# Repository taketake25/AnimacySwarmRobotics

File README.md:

# StudySwarmRobotics
群ロボットの勉強のために、5cm角のを作成します。赤外線での近距離通信可能。

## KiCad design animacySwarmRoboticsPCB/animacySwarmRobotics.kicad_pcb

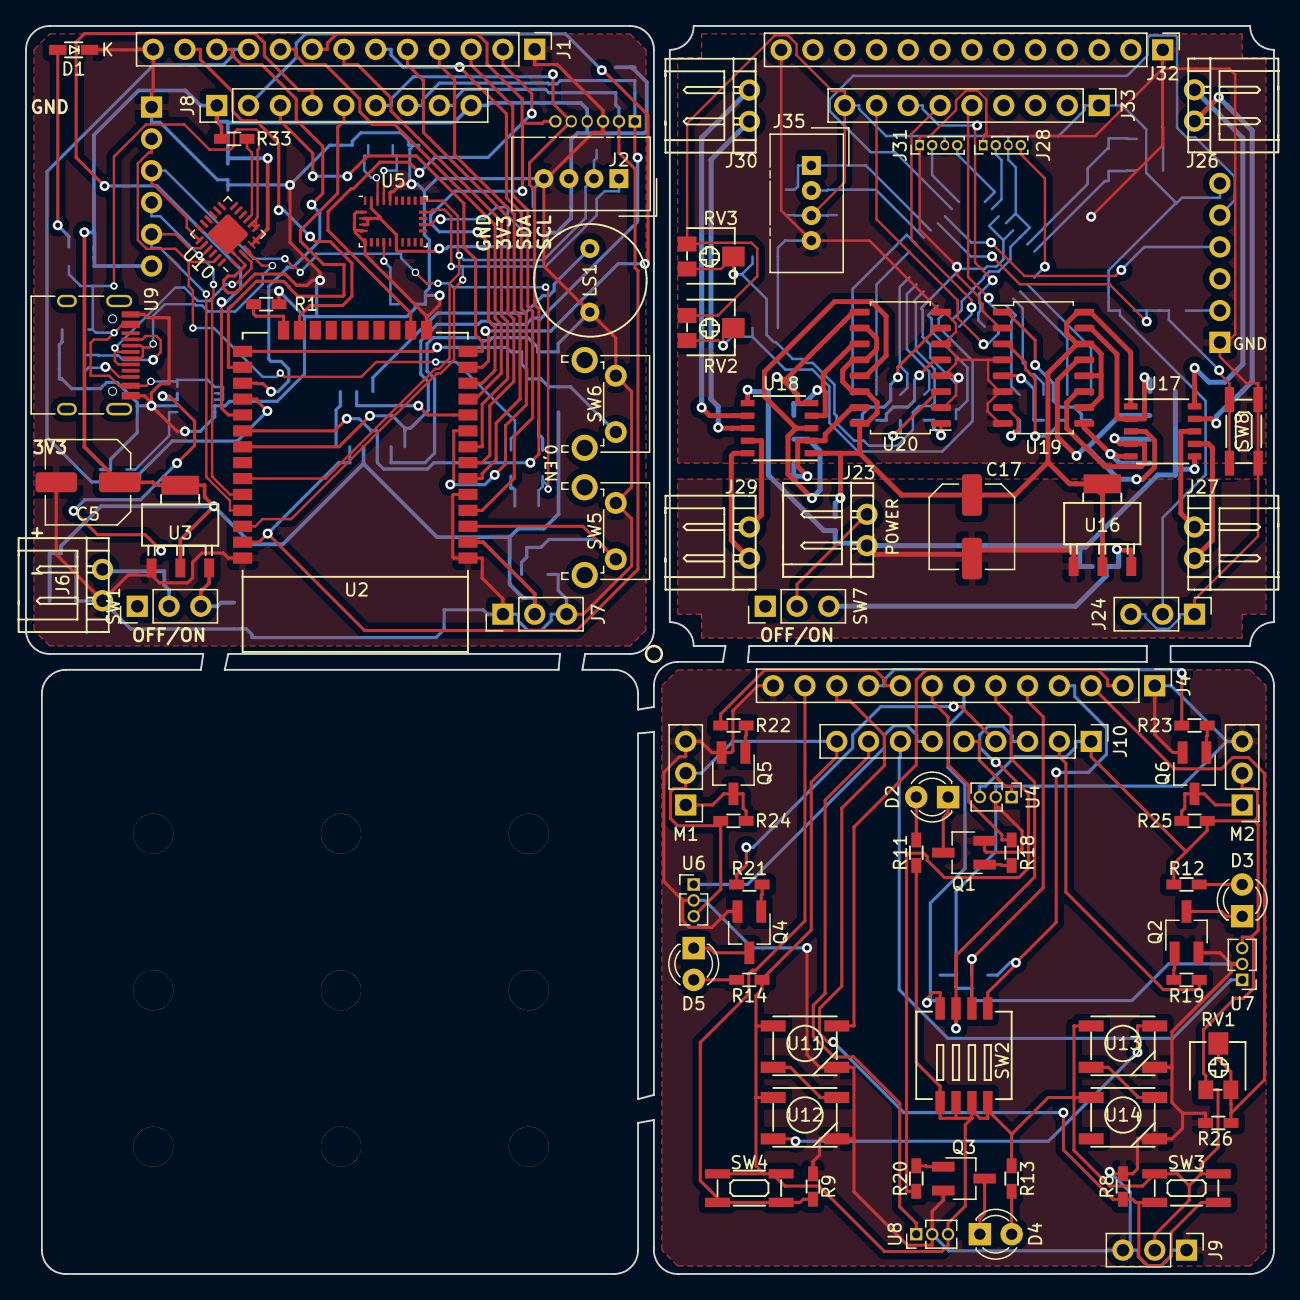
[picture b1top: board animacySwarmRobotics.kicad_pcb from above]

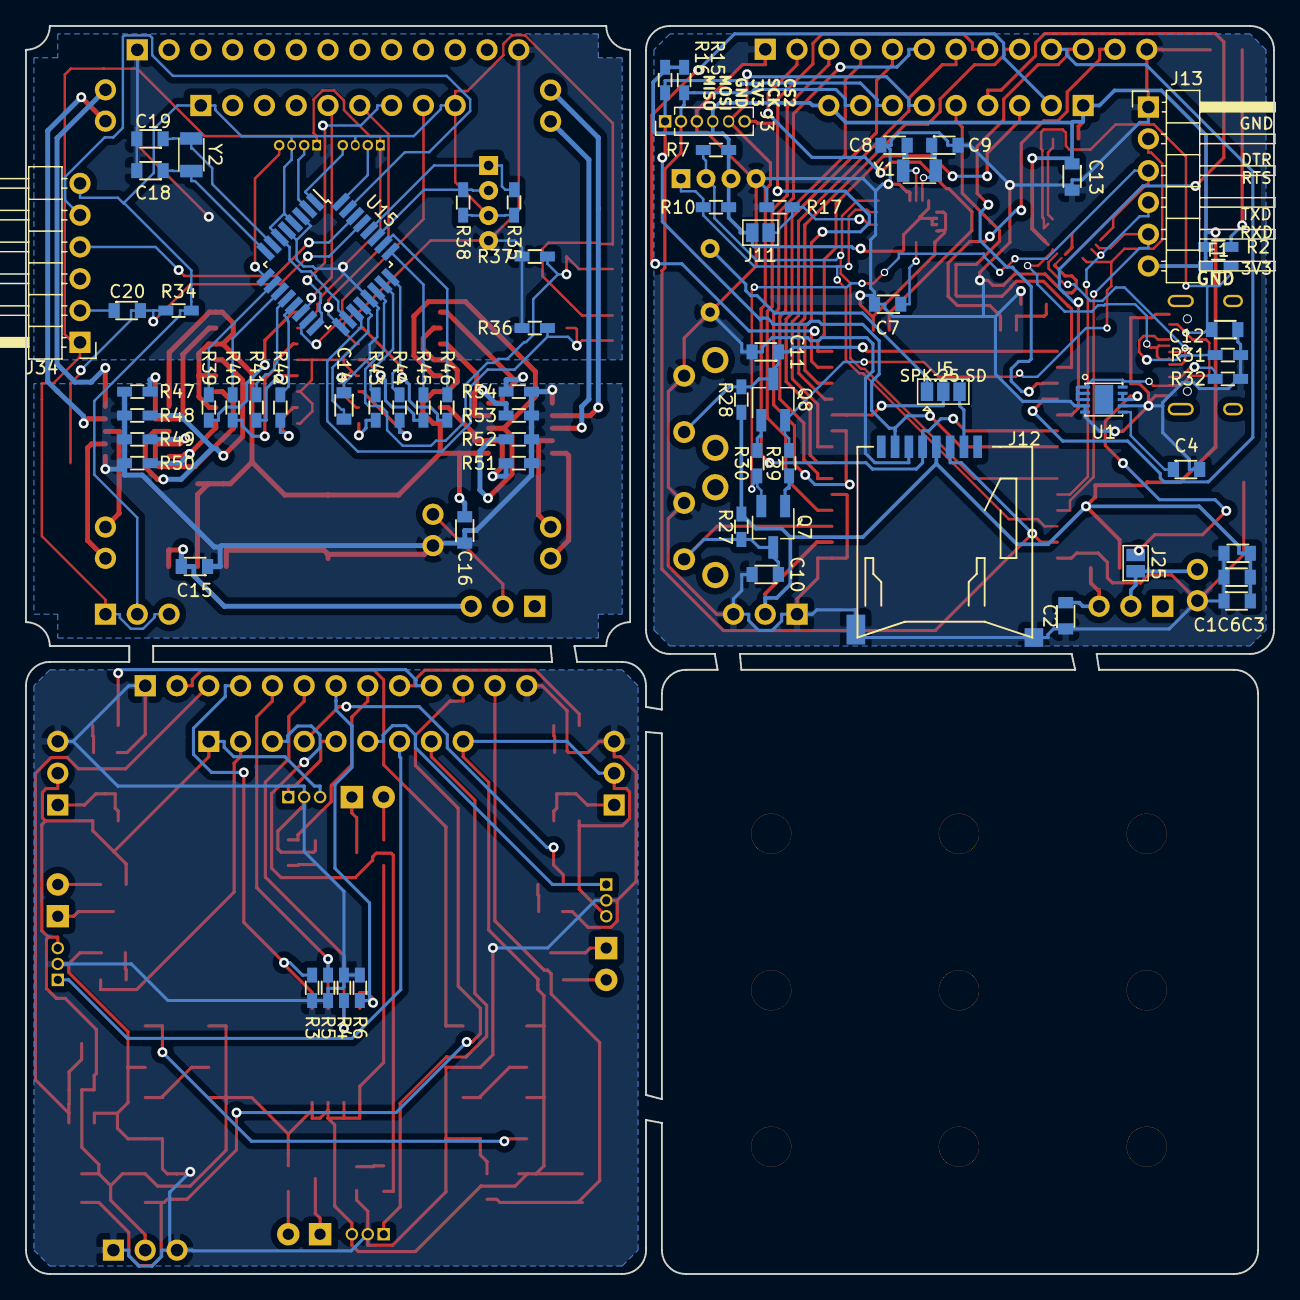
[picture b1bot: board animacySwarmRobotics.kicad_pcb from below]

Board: 2 copper layers, 99.7 x 99.7 mm, 159 parts (69 on the bottom side), 145 nets.

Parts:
C1: 1u; SMD-2012
C2, C3, C6, C15, C16: C; SMD-2012
C4, C7, C8, C9, C12, C13, C14, C18, C19, C20: C_Small; SMD-2012
C5, C17: CP; C_Elec_6.3x7.7
C10, C11: 1n; SMD-2012
D1: LED; 2012LED
D2, D3, D4, D5: LED; LED_D3.0mm
F1: Polyfuse_Small; SMD-1608
J1, J4, J32: Conn_01x13; PinHeader_1x13_P2.54mm_Vertical
J2, J35: Conn_01x04; NS-Tech_Grove_1x04_P2mm_Vertical
J3: Conn_01x06; PinHeader_1x06_P1.27mm_Vertical
J5: Conn_01x03; SolderJumper-3_P1.3mm_Open_Pad1.0x1.5mm
J6, J23, J26, J27, J29, J30: Conn_01x02; Connector_EH_2pin
J7, J9, J24: Conn_01x03; PinHeader_1x03_P2.54mm_Vertical
J8, J10, J33: Conn_01x09; PinHeader_1x09_P2.54mm_Vertical
J11, J25: Conn_01x02; SolderJumper-2_P1.3mm_Open_Pad1.0x1.5mm
J12: Micro_SD_Card_Det_Hirose_DM3AT; SD_DM3AT-SF-PEJMS
J13, J34: Conn_01x06; PinHeader_1x06_P2.54mm_Horizontal
J14, J15, J16, J17, J18, J19, J20, J21, J22: Conn_01x01; HOLE_3.2mm_nopad
J28, J31: Conn_01x04; PinHeader_1x04_P1.00mm_Vertical
LS1: Speaker; small_speaker
M1, M2: Motor_Servo; PinHeader_1x03_P2.54mm_Vertical
Q1, Q2, Q3, Q4, Q5, Q6, Q7, Q8: Q_NPN_BEC; SC-59_Handsoldering
R1, R28: 5K; SMD-1608
R2: 2K; SMD-1608
R3, R4, R5, R6: 1k; SMD-1608
R7, R10, R17: 2.2K; SMD-1608
R8, R9: 470; SMD-1608
R11, R12, R13, R14, R15, R16, R18, R19, R20, R21, R22, R23, R24, R25: R; SMD-1608
R26, R31, R32, R33, R34, R35, R36, R37, R38, R39, R40, R41, R42, R43, R44, R45, R46, R47, R48, R49, R50, R51, R52, R53, R54: 1K; SMD-1608
R27, R29, R30: 12K; SMD-1608
RV1, RV2, RV3: R_POT; S_POT_SMD
SW1, SW7: SW_SPDT; PinHeader_1x03_P2.54mm_Vertical
SW2: DIP_SW_4; EHS104LD
SW3, SW4, SW8: SW_Push; SMD_SW
SW5, SW6: SW_Push; SW_Tactile_SPST_Angled_PTS645Vx39-2LFS
U1: MCP73855T-I; MCP73855
U2: ESP32; ESP-WROOM-32
U3, U16: AMS1117CD-3.3; AZ1086H
U4, U6, U7, U8: OSRB38C9AA; PinHeader_1x03_P1.27mm_Vertical
U5: BNO085; LGA-28_5.2x3.8mm_P0.5mm
U9: TypeC; USB_C_Receptacle_HRO_TYPE-C-31-M-12
U10: CP2104; QFN-24-1EP_4x4mm_P0.5mm_EP2.6x2.6mm
U11, U12, U13, U14: WS2812B
U15: ATmega328P-AU; TQFP-32_7x7mm_P0.8mm
U17, U18: LV8548MC; SSOP-10_3.9x4.9mm_P1.00mm
U19, U20: TLP293-4; SOIC-16_4.55x10.3mm_P1.27mm
Y1, Y2: Crystal; FC-135

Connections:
+3V3: C1.2, C3.1, C5.1, C6.1, C13.2, F1.2, J2.3, J3.4, J7.2, J8.1, J8.9, J11.2, J12.4, J13.6, R2.2, R7.1, R10.1, R15.1, R16.1, R27.1, R28.2, R33.2, U2.2, U3.2, U5.3, U5.4, U5.11, U5.28, U10.5, U10.6
+6V: C2.1, SW1.3, U3.3
/CS1: J5.3, J12.2
/D+: U9.A6, U9.B6, U10.3
/D-: U9.A7, U9.B7, U10.4
/DTR: J13.2, Q8.2, R29.2, U10.23
/EN: C10.2, Q7.3, R27.2, SW5.2, U2.3
/IO0: C11.2, Q8.3, R28.1, SW6.2, U2.25
/IO2: R1.2, U2.24
/IO4: J8.5, U2.26
/IO5: J8.4, U2.29
/IO12: J8.3, U2.14
/IO14: J8.2, U2.13
/IO15: J1.12, U2.23
/IO16: J1.11, U2.27
/IO17: J1.10, U2.28
/IO25: J5.2, U2.10
/IO26: J1.9, U2.11
/IO27: J1.8, J3.6, U2.12
/IO32: J1.7, U2.8
/IO33: J1.6, U2.9
/IO34: J1.4, U2.6
/IO35: J1.5, U2.7
/LEDs: J1.2, U2.16
/LiPo+: J6.2, J25.2, SW1.2
/MISO: J3.1, J8.7, J12.7, R16.2, U2.31
/MOSI: J3.2, J8.8, J12.3, R15.2, U2.37
/POT1: J1.3, U2.4
/RTS: J13.3, Q7.2, R30.2, U10.19
/RXD: J13.5, U2.35, U10.20
/S3V3: J9.2, J10.1, J10.9, M1.2, M2.2, R11.1, R12.1, R13.1, R14.1, R24.1, R25.1, RV1.1, SW2.1, SW2.2, SW2.3, SW2.4, SW3.1, SW4.1, U4.3, U6.3, U7.3, U8.3, U11.1, U12.1, U13.1, U14.1
/SCK: J3.5, J8.6, J12.5, U2.30
/SCL: J2.1, R10.2, U2.36, U5.19
/SDA: J2.2, R7.2, U2.33, U5.20
/SDIP1: J4.4, R3.1, SW2.8
/SDIP2: J4.5, R5.1, SW2.7
/SDIP3: J4.6, R4.1, SW2.6
/SDIP4: J4.7, R6.1, SW2.5
/SGND: J4.1, J4.13, J9.1, J9.3, M1.3, M2.3, Q1.2, Q2.2, Q3.2, Q4.2, Q5.2, Q6.2, R3.2, R4.2, R5.2, R6.2, R8.2, R9.2, R26.2, U4.2, U6.2, U7.2, U8.2, U11.3, U12.3, U13.3, U14.3
/SIR1: J4.8, R18.1
/SIR2: J10.2, R19.1
/SIR3: J10.3, R20.1
/SIR4: J10.4, R21.1
/SIRRecv1: J10.5, U4.1
/SIRRecv2: J10.6, U6.1
/SIRRecv3: J10.7, U7.1
/SIRRecv4: J10.8, U8.1
/SLEDs: J4.2, U11.4
/SPOT: J4.3, R26.1, RV1.2, RV1.3
/SSERVO1: J4.9, R22.1
/SSERVO2: J4.10, R23.1
/SSW1: J4.11, R8.1, SW3.2
/SSW2: J4.12, R9.1, SW4.2
/Speaker1: J5.1, LS1.2
/TXD: J13.4, U2.34, U10.21
/VBUS: C12.1, F1.1, U1.1, U1.2, U1.3, U1.10, U9.A4, U9.A9, U9.B4, U9.B9, U10.7, U10.8
/motorBase/3V34: J24.2, J28.3, J31.3, J33.1, J33.9, J34.6, J35.3, R34.1, R35.1, R38.1, RV2.1, RV3.1, U15.4, U15.6, U15.18
/motorBase/BLIN1: R43.1, U15.23
/motorBase/BLIN2: R44.1, U15.24
/motorBase/BRIN1: R45.1, U15.25
/motorBase/BRIN2: R46.1, U15.26
/motorBase/CS4: J33.5, U15.14
/motorBase/DTR4: C20.2, J34.2
/motorBase/ENC1A: J31.2, U15.32
/motorBase/ENC1B: J31.4, U15.1
/motorBase/ENC2A: J28.2, U15.2
/motorBase/ENC2B: J28.4, U15.9
/motorBase/FLIN1: R39.1, U15.10
/motorBase/FLIN2: R40.1, U15.11
/motorBase/FRIN1: R41.1, U15.12
/motorBase/FRIN2: R42.1, U15.13
/motorBase/GND4: C14.2, C18.1, C19.1, J24.1, J24.3, J28.1, J31.1, J32.1, J32.13, J34.1, J35.4, R36.2, R37.2, SW8.2, U15.3, U15.5, U15.21, U19.2, U19.4, U19.6, U19.8, U20.2, U20.4, U20.6, U20.8
/motorBase/M3V3: C16.1, C17.1, U16.2, U17.1, U18.1, U19.10, U19.12, U19.14, U19.16, U20.10, U20.12, U20.14, U20.16
/motorBase/MBLIN1: R51.1, U18.2, U20.15
/motorBase/MBLIN2: R52.1, U18.3, U20.13
/motorBase/MBLOUT1: J29.1, U18.10
/motorBase/MBLOUT2: J29.2, U18.9
/motorBase/MBRIN1: R53.1, U18.4, U20.11
/motorBase/MBRIN2: R54.1, U18.5, U20.9
/motorBase/MBROUT1: J30.1, U18.8
/motorBase/MBROUT2: J30.2, U18.7
/motorBase/MFLIN1: R47.1, U17.2, U19.15
/motorBase/MFLIN2: R48.1, U17.3, U19.13
/motorBase/MFLOUT1: J26.1, U17.10
/motorBase/MFLOUT2: J26.2, U17.9
/motorBase/MFRIN1: R49.1, U17.4, U19.11
/motorBase/MFRIN2: R50.1, U17.5, U19.9
/motorBase/MFROUT1: J27.1, U17.8
/motorBase/MFROUT2: J27.2, U17.7
/motorBase/MGND: C15.2, C16.2, C17.2, J23.1, R47.2, R48.2, R49.2, R50.2, R51.2, R52.2, R53.2, R54.2, U16.1, U17.6, U18.6
/motorBase/MISO4: J33.7, U15.16
/motorBase/MOSI4: J33.8, U15.15
/motorBase/MVcc: C15.1, SW7.3, U16.3
/motorBase/POT14: R36.1, RV2.2, RV2.3, U15.19
/motorBase/POT24: R37.1, RV3.2, RV3.3, U15.22
/motorBase/RXD4: J34.5, U15.31
/motorBase/SCK4: J33.6, U15.17
/motorBase/SCL4: J35.1, R35.2, U15.28
/motorBase/SDA4: J35.2, R38.2, U15.27
/motorBase/TXD4: J34.4, U15.30
GND: C1.1, C2.2, C3.2, C4.1, C5.2, C6.2, C7.1, C8.1, C9.1, C10.1, C11.1, C12.2, C13.1, D1.1, J1.1, J1.13, J2.4, J3.3, J6.1, J7.1, J7.3, J12.6, J12.11, J13.1, LS1.1, R1.1, R17.2, R31.2, R32.1, SW5.1, SW6.1, U1.4, U1.5, U1.7, U2.1, U2.5, U2.15, U2.38, U3.1, U5.2, U5.5, U5.6, U5.25, U9.A1, U9.A12, U9.B1, U9.B12, U10.2, U10.25
unnamed: C4.2, U1.6
unnamed: C7.2, U5.9
unnamed: C8.2, U5.26, Y1.1
unnamed: C9.2, U5.27, Y1.2
unnamed: C14.1, U15.20
unnamed: C18.2, U15.8, Y2.1
unnamed: C19.2, U15.7, Y2.2
unnamed: C20.1, R34.2, SW8.1, U15.29
unnamed: D1.2, R2.1
unnamed: D2.1, Q1.3
unnamed: D2.2, R11.2
unnamed: D3.1, Q2.3
unnamed: D3.2, R12.2
unnamed: D4.1, Q3.3
unnamed: D4.2, R13.2
unnamed: D5.1, Q4.3
unnamed: D5.2, R14.2
unnamed: J11.1, R17.1, U5.17
unnamed: J23.2, SW7.2
unnamed: J25.1, U1.8, U1.9
unnamed: M1.1, Q5.3, R24.2
unnamed: M2.1, Q6.3, R25.2
unnamed: Q1.1, R18.2
unnamed: Q2.1, R19.2
unnamed: Q3.1, R20.2
unnamed: Q4.1, R21.2
unnamed: Q5.1, R22.2
unnamed: Q6.1, R23.2
unnamed: Q7.1, R29.1
unnamed: Q8.1, R30.1
unnamed: R31.1, U9.A5
unnamed: R32.2, U9.B5
unnamed: R33.1, U10.9
unnamed: R39.2, U19.1
unnamed: R40.2, U19.3
unnamed: R41.2, U19.5
unnamed: R42.2, U19.7
unnamed: R43.2, U20.1
unnamed: R44.2, U20.3
unnamed: R45.2, U20.5
unnamed: R46.2, U20.7
unnamed: U11.2, U12.4
unnamed: U12.2, U13.4
unnamed: U13.2, U14.4

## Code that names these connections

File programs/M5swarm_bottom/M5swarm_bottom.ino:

#include <SPI.h>

// 3,5,6,9,10,11
#define FRIN1 8
//#define FRIN1 10 // PWM
#define FRIN2 9 // PWM
#define FLIN1 6 // PWM
#define FLIN2 7
//#define BLIN1 3 // PWM
#define BLIN1 14
#define BLIN2 15
//#define BRIN1 5 // PWM
#define BRIN1 16
#define BRIN2 17
#define SDA 18
#define SCL 19
//#define ENC1A 2 // ×
//#define ENC1B 3 // ×
#define ENC2A 4
//#define ENC2B 5 // ×
#define CS 10 // ×
//#define CS 2
#define MOSI 11
#define MISO 12
#define SCK 13
#define POT1 ADC6
#define POT2 ADC7


int count = 0;
unsigned long startTime = 0;
unsigned long timer = 0;
bool timerFlag = false;
int cmdSpeedReceived = 0;
int cmdDirecReceived = 0;
int cmdRotateReceived = 0;
bool moving = false;
bool rotating = false;
int8_t speed = 0;
int8_t speedMotors[8] = {0};
int8_t motorPins[8] = {FLIN2,FLIN1,FRIN1,FRIN2,BRIN2,BRIN1,BLIN1,BLIN2};


#define FRONT 0
#define BACK 1

uint8_t recvD;
uint8_t recvS;
uint8_t recvR;

void setup() {
  Serial.begin(115200);
  Serial.println("run!!");

  pinMode(CS, OUTPUT);
  SPCR |= bit(SPE);
  pinMode(MISO, OUTPUT);

  pinMode(FRIN1, OUTPUT);
  pinMode(FRIN2, OUTPUT);
  pinMode(FLIN1, OUTPUT);
  pinMode(FLIN2, OUTPUT);
  pinMode(BRIN1, OUTPUT);
  pinMode(BRIN2, OUTPUT);
  pinMode(BLIN1, OUTPUT);
  pinMode(BLIN2, OUTPUT);

  //  SPI.begin();
  //  SPI.beginTransaction(SPISetting(8000000, MSBFIRST, SPI_MODE3));
  SPI.attachInterrupt();
  startTime = millis();
}

ISR(SPI_STC_vect) {
//  cmdDirecReceived = false;
//  cmdSpeedReceived = false;
  switch (char(SPDR)) {
    case 's': cmdSpeedReceived = 1; break; // s
    case 'd': cmdDirecReceived = 1; break; // d
    case 'r': cmdRotateReceived = 1; break; // d
    default : 
      if(cmdDirecReceived==1){recvD = uint8_t(SPDR);cmdDirecReceived=2;}
      if(cmdSpeedReceived==1){recvS = uint8_t(SPDR);cmdSpeedReceived=2;}
      if(cmdRotateReceived==1){recvR = uint8_t(SPDR);cmdRotateReceived=2;}
      break;
  }

//  Serial.print(recvD);
//  Serial.print("  ");
//  Serial.print(recvS);
//  Serial.print("  ");
  Serial.print(SPDR);
  Serial.print("  ");
  Serial.println(char(SPDR));
}

void loop() {
  float rad; // = ((recvD*360)/256-180)*3.141592/180.0;
  static int a,b;

//  Serial.println(recv);
  if (cmdSpeedReceived==2) {
    speed = recvS-10;
    speed = speed * sqrt(2);
    Serial.println(speed);

    cmdSpeedReceived = 0;
    startTime = millis();
    moving = true;
    rotating = false;
  }
  if (cmdDirecReceived==2) {
    rad = (float(recvD)*2)*3.1415 / 180.0 + 3.1415 / 4.0;
    cmdDirecReceived = 0;
    Serial.println(rad);
  }
  if (cmdRotateReceived==2) {
    rad = (float(recvR)*2)*3.1415 / 180.0 + 3.1415 / 4.0;
    Serial.println(rad);

    cmdRotateReceived = 0;
    startTime = millis();
    moving = false;
    rotating = true;
  }
  timer = millis();


  if(moving && ((timer - startTime) > 250)){
    Serial.print(a);
    Serial.print("  ");
    Serial.print(b);
    Serial.print("  ");
    Serial.println(rad);
    Serial.println(speed);
    Serial.println("stop");
    speed = 0; 
    moving = false; 
    actMotorFB(FRONT, 0, 0);
    actMotorFB(BACK , 0, 0);
  }
  
  if(rotating && ((timer - startTime) > 250)){
    Serial.println("stop rotate");
    speed = 0; 
    rotating = false;
    actMotorFB(FRONT, 0, 0);
    actMotorFB(BACK , 0, 0);
  }

//  rad += 0.1;

  a = int(speed * cos(rad)); // -10~10の速度に変換
  b = int(speed * sin(rad));
  if(abs(a) > 10) a = 0;
  if(abs(b) > 10) b = 0;


  if(rotating){
    while(count < 10){
      count++;
      if(recvR == 2){a = -7;b = 7;}
      else{a = 7;b = -7;}
      actMotorFB(FRONT, a, b);
      delay(1);
    }
    count = 0;
  
    while(count < 10){
      count++;
      if(recvR == 2){a = -7;b = 7;}
      else{a = 7;b = -7;}
      actMotorFB(BACK , a, b);
      delay(1);
    }
    count = 0;
  }
  


  if(moving){
    while(count < 10){
      count++;
//    actMotorFB(FRONT, 10, -10);
      actMotorFB(FRONT, a, b);
      delay(1);
    }
    count = 0;
  
    while(count < 10 && moving){
      count++;
//    actMotorFB(BACK, -10, 10);
      actMotorFB(BACK, b, a);
      delay(1);
    }
    count = 0;  
  }

  
}



void actMotorFB(int ForB, int speedL, int speedR) {
  int R1, R2, L1, L2;
  int offsetIndex = 0;
  if (ForB == FRONT) {
    L1 = FLIN1; L2 = FLIN2;
    R1 = FRIN2; R2 = FRIN1;
    offsetIndex = 0;
  } else {
    R1 = BLIN2; R2 = BLIN1;
    L1 = BRIN1; L2 = BRIN2;
    offsetIndex = 4;
  }

  uint8_t outL1, outL2;
  uint8_t outR1, outR2;

  if (speedL >= 0) {
    speedMotors[0 + offsetIndex] = speedL;
    speedMotors[1 + offsetIndex] = 0;
  } else {
    speedMotors[0 + offsetIndex] = 0;
    speedMotors[1 + offsetIndex] = -speedL;
  }
  if (speedR >= 0) {
    speedMotors[2 + offsetIndex] = speedR;
    speedMotors[3 + offsetIndex] = 0;
  } else {
    speedMotors[2 + offsetIndex] = 0;
    speedMotors[3 + offsetIndex] = -speedR;
  }

  for(int i=0; i<4; i++){ // software PWM
//    int8_t temp = int(count/speedMotors[i + offsetIndex]);
    if(abs(count) < speedMotors[i + offsetIndex])digitalWrite(motorPins[i + offsetIndex], HIGH);
    else digitalWrite(motorPins[i + offsetIndex], LOW);
  }


//  Serial.print(abs(count));
//  Serial.print("\t");
//  Serial.print(speedL);
//  Serial.print("\t");
//  Serial.print(speedR);
//  Serial.print("\t");
//  Serial.print(speedMotors[0 + offsetIndex]);
//  Serial.print("\t");
//  Serial.print(speedMotors[1 + offsetIndex]);
//  Serial.print("\t");
//  Serial.print(speedMotors[2 + offsetIndex]);
//  Serial.print("\t");
//  Serial.println(speedMotors[3 + offsetIndex]);

}




//#define FRIN1 PB0
//#define FRIN2 PB1
//#define FLIN1 PD6
//#define FLIN2 PD7
//#define BLIN1 PC0
//#define BLIN2 PC1
//#define BRIN1 PC2
//#define BRIN2 PC3
//#define SDA PC4
//#define SCL PC5
//#define ENC1A PD2
//#define ENC1B PD3
//#define ENC2A PD4
//#define ENC2B PD5
//#define CS PB2
//#define MOSI PB3
//#define MISO PB4
//#define SCK PB5
//#define POT1 ADC6
//#define POT2 ADC7



/*
  digitalWrite(motorPins[0],HIGH);
  digitalWrite(motorPins[1],LOW);
  digitalWrite(motorPins[2],HIGH);
  digitalWrite(motorPins[3],LOW);
  digitalWrite(motorPins[4],HIGH);
  digitalWrite(motorPins[5],LOW);
  digitalWrite(motorPins[6],HIGH);
  digitalWrite(motorPins[7],LOW);
  delay(1000);
  for(int i=0;i<8;i++)digitalWrite(motorPins[i],LOW);
  delay(1000);
  digitalWrite(motorPins[0],LOW);
  digitalWrite(motorPins[1],HIGH);
  digitalWrite(motorPins[2],LOW);
  digitalWrite(motorPins[3],HIGH);
  digitalWrite(motorPins[4],LOW);
  digitalWrite(motorPins[5],HIGH);
  digitalWrite(motorPins[6],LOW);
  digitalWrite(motorPins[7],HIGH);
  delay(1000);
  for(int i=0;i<8;i++)digitalWrite(motorPins[i],LOW);
  delay(1000);*/

 


/*
  if (speedL >= 0) {
//    outL1= 255 - speedL;
//    outL2= 255;
    outL1= 2*speedL;
    outL2= 0;
  } else {
    outL1= 0;
    outL2= -2*speedL;
  }
  analogWrite(L1, outL1);
  analogWrite(L2, outL2);

  if (speedR >= 0) {
//    outR1= 255 - speedR;
//    outR2= 255;
    outR1= 2*speedR;
    outR2= 0;
  } else {
    outR1= 0;
    outR2= -2*speedR;
  }
    analogWrite(R1, outR1);
    analogWrite(R2, outR2);
*/

//  char buff[100];
//  memset(buff, 0, sizeof(buff));
//  sprintf(buff, "outL1:%d, outL2:%d, outR1:%d, outR2:%d", outL1, outL2, outR1, outR2);
//  Serial.print(buff);

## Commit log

2021-04-22 finish creating pcb data
2021-04-22 fix schematic because i changed failue project...
2021-05-01 clean schematics
2021-05-10 commit something
2021-11-29 this version was implimented for M5Stack Contest
2021-11-29 Create LICENSE
2021-11-29 add lack script to be able to move M5swarm
